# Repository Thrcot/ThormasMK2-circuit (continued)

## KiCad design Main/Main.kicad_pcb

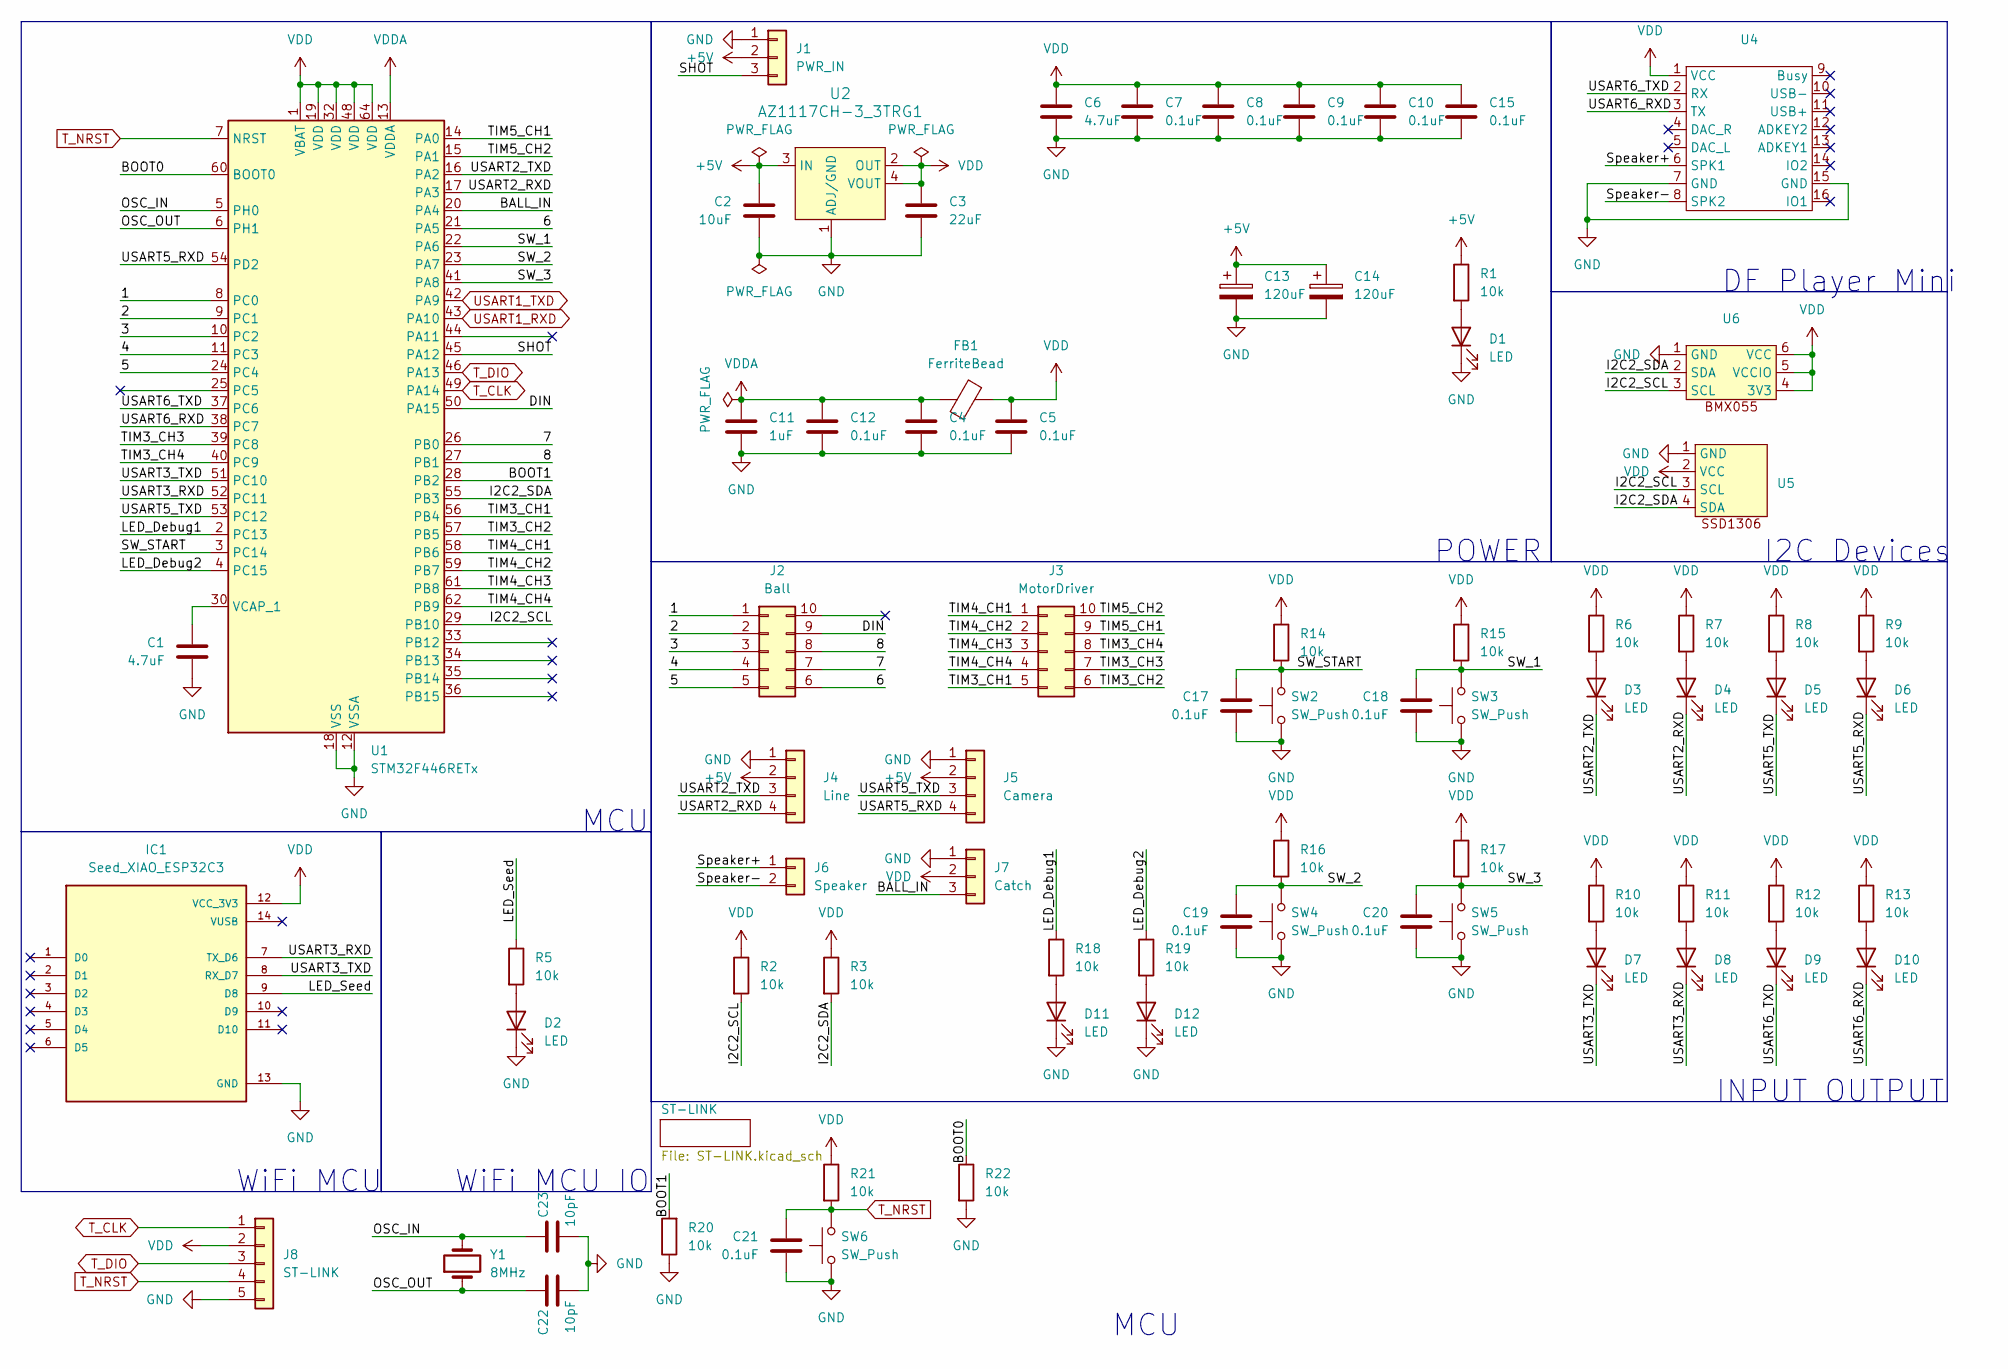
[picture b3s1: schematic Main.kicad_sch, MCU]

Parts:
C1, C6: 4.7uF; C_0603_1608Metric
C2: 10uF; C_0603_1608Metric
C3: 22uF; C_0603_1608Metric
C4, C5, C7, C8, C9, C10, C12, C15, C17, C18, C19, C20, C21: 0.1uF; C_0402_1005Metric
C11: 1uF; C_0603_1608Metric
C13, C14: 120uF; CP_Radial_D10.0mm_P5.00mm
C22, C23: 10pF; C_0402_1005Metric
D1, D2, D3, D4, D5, D6, D7, D8, D9, D10, D11, D12: LED; LED_0603_1608Metric
FB1: FerriteBead; L_0603_1608Metric
IC1: Seed_XIAO_ESP32C3; PARTREV 23/05/2022
J1: PWR_IN; JST_XH_S3B-XH-A_1x03_P2.50mm_Horizontal
J2: Ball; IDC-Header_2x05_P2.54mm_Vertical
J3: MotorDriver; IDC-Header_2x05_P2.54mm_Vertical
J4: Line; JST_XH_S4B-XH-A_1x04_P2.50mm_Horizontal
J5: Camera; JST_XH_S4B-XH-A_1x04_P2.50mm_Horizontal
J6: Speaker; JST_XH_B2B-XH-A_1x02_P2.50mm_Vertical
J7: Catch; JST_XH_S3B-XH-A_1x03_P2.50mm_Horizontal
J8: ST-LINK; PinHeader_1x05_P2.54mm_Horizontal
R1, R2, R3, R5, R6, R7, R8, R9, R10, R11, R12, R13, R14, R15, R16, R17, R18, R19, R20, R21, R22: 10k; R_0603_1608Metric
SW2, SW3, SW4, SW5, SW6: SW_Push; SW_PUSH_6mm
U1: STM32F446RETx; LQFP-64_10x10mm_P0.5mm
U2: AZ1117CH-3_3TRG1; SOT-223; MPN AZ1117CH-3.3TRG1
U4: DFPlayerMini
U5: SSD1306
U6: BMX055DIP
Y1: 8MHz; Crystal_HC49-4H_Vertical

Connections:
+5V: C2.1, C13.1, C14.1, J1.2, J4.2, J5.2, R1.1, U2.3 (IN); also elsewhere on the board
/1: J2.1, U1.8 (PC0)
/2: J2.2, U1.9 (PC1)
/3: J2.3, U1.10 (PC2)
/4: J2.4, U1.11 (PC3)
/5: J2.5, U1.24 (PC4)
/6: J2.6, U1.21 (PA5)
/7: J2.7, U1.26 (PB0)
/8: J2.8, U1.27 (PB1)
/BALL_IN: J7.3, U1.20 (PA4)
/BOOT0: R22.1, U1.60 (BOOT0)
/BOOT1: R20.2, U1.28 (PB2)
/DIN: J2.9, U1.50 (PA15)
/I2C2_SCL: R2.2, U1.29 (PB10), U5.3 (SCL), U6.3 (SCL)
/I2C2_SDA: R3.2, U1.55 (PB3), U5.4 (SDA), U6.2 (SDA)
/LED_Debug1: R18.1, U1.2 (PC13)
/LED_Debug2: R19.1, U1.4 (PC15)
/LED_Seed: IC1.9 (D8), R5.1
/OSC_IN: C23.1, U1.5 (PH0), Y1.2
/OSC_OUT: C22.1, U1.6 (PH1), Y1.1
/SHOT: J1.3, U1.45 (PA12)
/SW_1: C18.1, R15.2, SW3.2, U1.22 (PA6)
/SW_2: C19.1, R16.2, SW4.2, U1.23 (PA7)
/SW_3: C20.1, R17.2, SW5.2, U1.41 (PA8)
/SW_START: C17.1, R14.2, SW2.2, U1.3 (PC14)
/Speaker+: J6.1, U4.6 (SPK1)
/Speaker-: J6.2, U4.8 (SPK2)
/TIM3_CH1: J3.5, U1.56 (PB4)
/TIM3_CH2: J3.6, U1.57 (PB5)
/TIM3_CH3: J3.7, U1.39 (PC8)
/TIM3_CH4: J3.8, U1.40 (PC9)
/TIM4_CH1: J3.1, U1.58 (PB6)
/TIM4_CH2: J3.2, U1.59 (PB7)
/TIM4_CH3: J3.3, U1.61 (PB8)
/TIM4_CH4: J3.4, U1.62 (PB9)
/TIM5_CH1: J3.9, U1.14 (PA0)
/TIM5_CH2: J3.10, U1.15 (PA1)
/USART2_RXD: D4.1 (K), J4.4, U1.17 (PA3)
/USART2_TXD: D3.1 (K), J4.3, U1.16 (PA2)
/USART3_RXD: D8.1 (K), IC1.7 (TX_D6), U1.52 (PC11)
/USART3_TXD: D7.1 (K), IC1.8 (RX_D7), U1.51 (PC10)
/USART5_RXD: D6.1 (K), J5.4, U1.54 (PD2)
/USART5_TXD: D5.1 (K), J5.3, U1.53 (PC12)
/USART6_RXD: D10.1 (K), U1.38 (PC7), U4.3 (TX)
/USART6_TXD: D9.1 (K), U1.37 (PC6), U4.2 (RX)
GND: C1.2, C2.2, C3.2, C4.2, C5.2, C6.2, C7.2, C8.2, C9.2, C10.2, C11.2, C12.2, C13.2, C14.2, C15.2, C17.2, C18.2, C19.2, C20.2, C21.2, C22.2, C23.2, D1.1 (K), D2.1 (K), D11.1 (K), D12.1 (K), IC1.13 (GND), J1.1, J4.1, J5.1, J7.1, J8.5, R20.1, R22.2, SW2.1, SW3.1, SW4.1, SW5.1, SW6.1, U1.12 (VSSA), U1.18 (VSS), U1.31 (VSS), U1.47 (VSS), U1.63 (VSS), U2.1 (ADJ/GND), U4.7 (GND), U4.15 (GND), U5.1 (GND), U6.1 (GND); also elsewhere on the board
unnamed: D1.2 (A), R1.2
unnamed: D2.2 (A), R5.2
unnamed: D3.2 (A), R6.2
unnamed: D4.2 (A), R7.2
unnamed: D5.2 (A), R8.2
unnamed: D6.2 (A), R9.2
unnamed: D7.2 (A), R10.2
unnamed: D8.2 (A), R11.2
unnamed: D9.2 (A), R12.2
unnamed: D10.2 (A), R13.2
unnamed: D11.2 (A), R18.2
unnamed: D12.2 (A), R19.2
unnamed: C1.1, U1.30 (VCAP_1)
T_CLK: J8.1, U1.49 (PA14); also elsewhere on the board
T_DIO: J8.3, U1.46 (PA13); also elsewhere on the board
T_NRST: C21.1, J8.4, R21.2, SW6.2, U1.7 (NRST); also elsewhere on the board
USART1_RXD: U1.43 (PA10); also elsewhere on the board
USART1_TXD: U1.42 (PA9); also elsewhere on the board
VDD: C3.1, C5.1, C6.1, C7.1, C8.1, C9.1, C10.1, C15.1, FB1.2, IC1.12 (VCC_3V3), J7.2, J8.2, R2.1, R3.1, R6.1, R7.1, R8.1, R9.1, R10.1, R11.1, R12.1, R13.1, R14.1, R15.1, R16.1, R17.1, R21.1, U1.1 (VBAT), U1.19 (VDD), U1.32 (VDD), U1.48 (VDD), U1.64 (VDD), U2.2 (OUT), U2.4 (VOUT), U4.1 (VCC), U5.2 (VCC), U6.4 (3V3), U6.5 (VCCIO), U6.6 (VCC); also elsewhere on the board
VDDA: C4.1, C11.1, C12.1, FB1.1, U1.13 (VDDA)

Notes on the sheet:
WiFi MCU IO
MCU
POWER
INPUT OUTPUT
DF Player Mini
WiFi MCU
I2C Devices

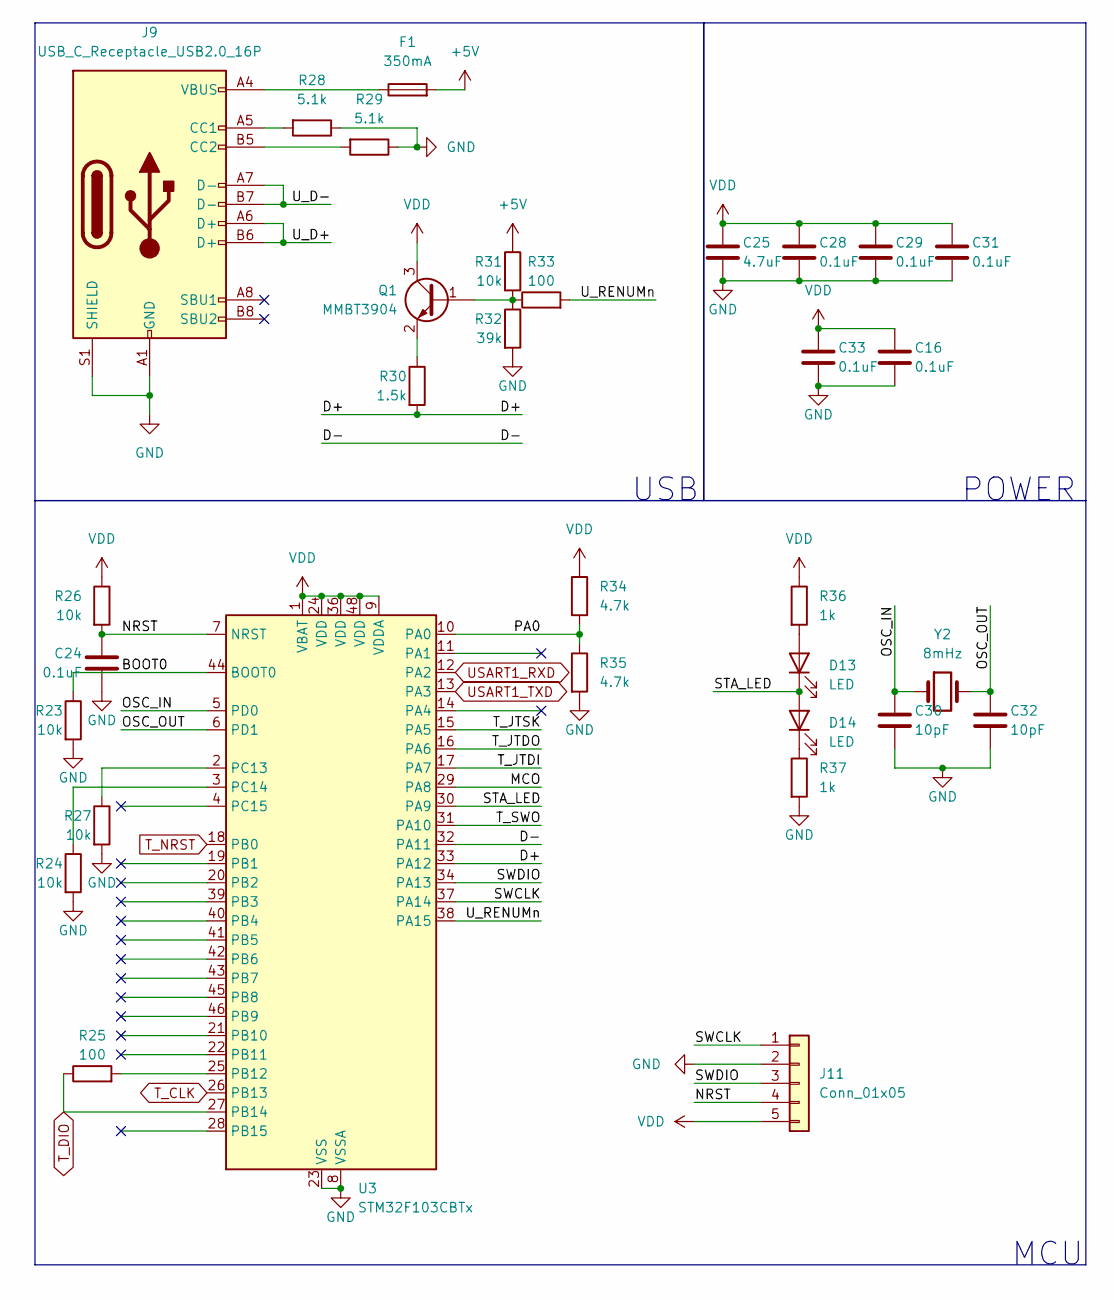
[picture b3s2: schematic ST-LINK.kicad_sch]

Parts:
C16, C24, C28, C29, C31, C33: 0.1uF; C_0402_1005Metric
C25: 4.7uF; C_0603_1608Metric
C30, C32: 10pF; C_0402_1005Metric
D13, D14: LED; LED_0603_1608Metric
F1: 350mA; Fuse_0402_1005Metric
J9: USB_C_Receptacle_USB2.0_16P; USB_C_Receptacle_GCT_USB4105-xx-A_16P_TopMnt_Horizontal
J11: Conn_01x05; PinHeader_1x05_P2.54mm_Vertical
Q1: MMBT3904; SOT-23
R23, R24, R26, R27, R31: 10k; R_0603_1608Metric
R25, R33: 100; R_0603_1608Metric
R28, R29: 5.1k; R_0603_1608Metric
R30: 1.5k; R_0603_1608Metric
R32: 39k; R_0603_1608Metric
R34, R35: 4.7k; R_0603_1608Metric
R36, R37: 1k; R_0603_1608Metric
U3: STM32F103CBTx; LQFP-48_7x7mm_P0.5mm
Y2: 8mHz; Crystal_HC49-4H_Vertical

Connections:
+5V: F1.2, R31.1; also elsewhere on the board
/ST-LINK/BOOT0: R23.1, U3.44 (BOOT0)
/ST-LINK/D+: R30.2, U3.33 (PA12)
/ST-LINK/D-: U3.32 (PA11)
/ST-LINK/MCO: U3.29 (PA8)
/ST-LINK/NRST: C24.1, J11.4, R26.2, U3.7 (NRST)
/ST-LINK/OSC_IN: C30.1, U3.5 (PD0), Y2.1
/ST-LINK/OSC_OUT: C32.1, U3.6 (PD1), Y2.2
/ST-LINK/PA0: R34.2, R35.1, U3.10 (PA0)
/ST-LINK/STA_LED: D13.1 (K), D14.2 (A), U3.30 (PA9)
/ST-LINK/SWCLK: J11.1, U3.37 (PA14)
/ST-LINK/SWDIO: J11.3, U3.34 (PA13)
/ST-LINK/T_JTDI: U3.17 (PA7)
/ST-LINK/T_JTDO: U3.16 (PA6)
/ST-LINK/T_JTSK: U3.15 (PA5)
/ST-LINK/T_SWO: U3.31 (PA10)
/ST-LINK/U_D+: J9.A6 (D+), J9.B6 (D+)
/ST-LINK/U_D-: J9.A7 (D-), J9.B7 (D-)
/ST-LINK/U_RENUMn: R33.2, U3.38 (PA15)
GND: C16.2, C24.2, C25.2, C28.2, C29.2, C30.2, C31.2, C32.2, C33.2, J9.A1 (GND), J9.A12 (GND), J9.B1 (GND), J9.B12 (GND), J9.S1 (SHIELD), J11.2, R23.2, R24.2, R27.2, R28.1, R29.1, R32.2, R35.2, R37.2, U3.8 (VSSA), U3.23 (VSS), U3.35 (VSS), U3.47 (VSS); also elsewhere on the board
unnamed: D13.2 (A), R36.2
unnamed: D14.1 (K), R37.1
unnamed: F1.1, J9.A4 (VBUS), J9.A9 (VBUS), J9.B4 (VBUS), J9.B9 (VBUS)
unnamed: J9.A5 (CC1), R28.2
unnamed: J9.B5 (CC2), R29.2
unnamed: Q1.1 (B), R31.2, R32.1, R33.1
unnamed: Q1.2 (E), R30.1
unnamed: R25.2, U3.25 (PB12)
unnamed: R27.1, U3.2 (PC13)
unnamed: R24.1, U3.3 (PC14)
T_CLK: U3.26 (PB13); also elsewhere on the board
T_DIO: R25.1, U3.27 (PB14); also elsewhere on the board
T_NRST: U3.18 (PB0); also elsewhere on the board
USART1_RXD: U3.12 (PA2); also elsewhere on the board
USART1_TXD: U3.13 (PA3); also elsewhere on the board
VDD: C16.1, C25.1, C28.1, C29.1, C31.1, C33.1, J11.5, Q1.3 (C), R26.1, R34.1, R36.1, U3.1 (VBAT), U3.9 (VDDA), U3.24 (VDD), U3.36 (VDD), U3.48 (VDD); also elsewhere on the board

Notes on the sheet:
MCU
POWER
USB

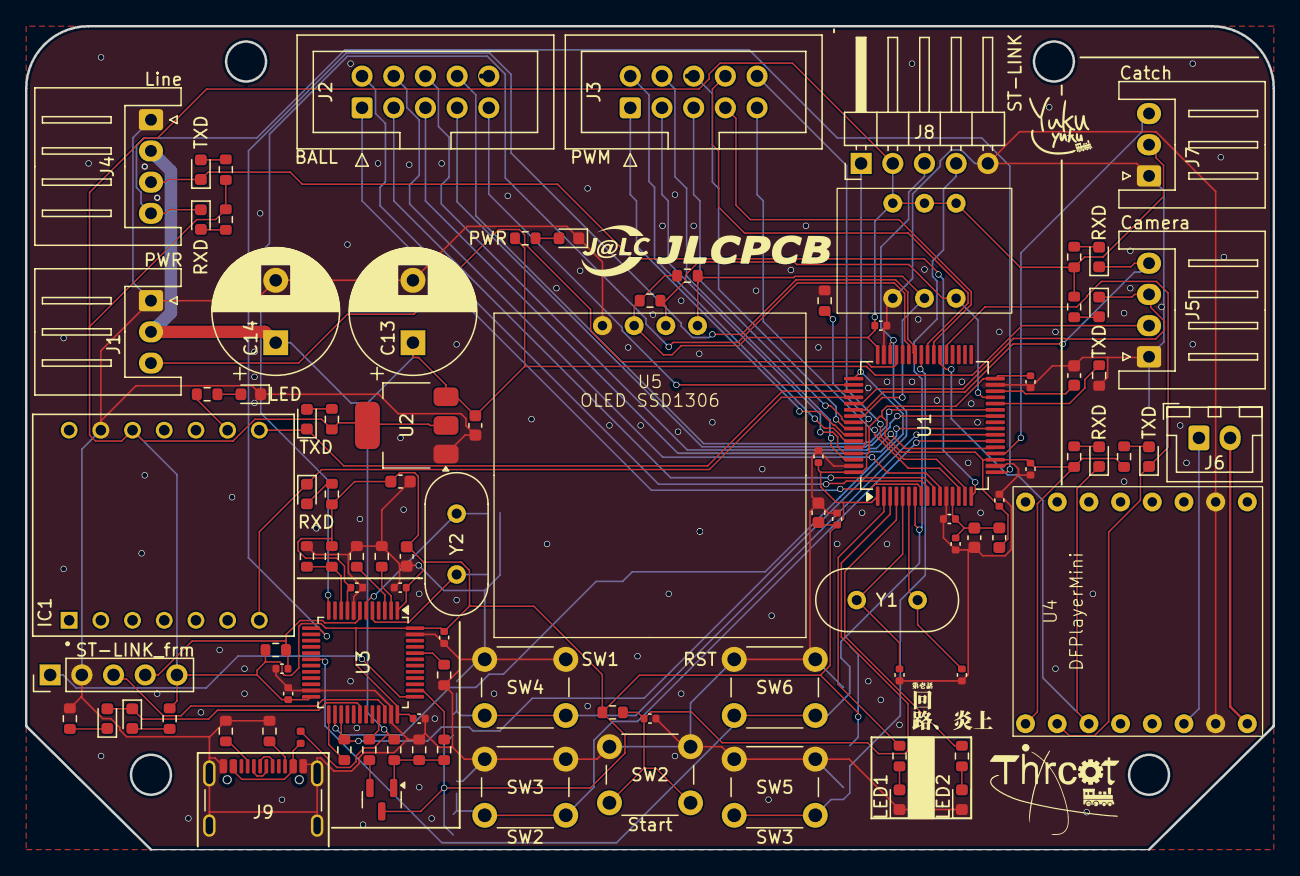
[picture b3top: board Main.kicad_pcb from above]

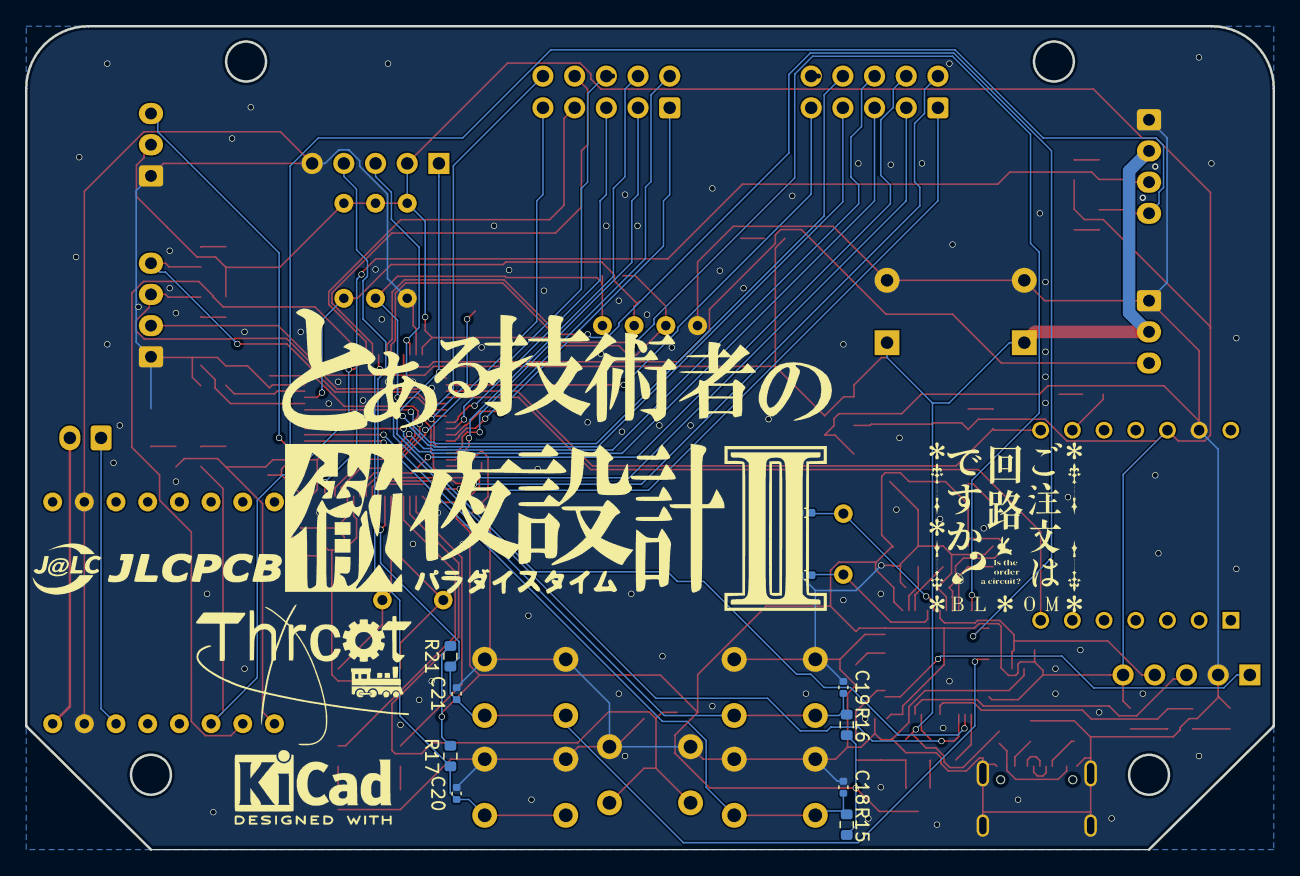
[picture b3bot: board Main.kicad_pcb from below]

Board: 2 copper layers, 100.0 x 66.0 mm, 108 parts (10 on the bottom side), 88 nets.

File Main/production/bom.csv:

Designator,Footprint,Quantity,Value,LCSC Part #
"C1, C25, C6",0603,3,4.7uF,
"C10, C12, C15, C16, C17, C18, C19, C20, C21, C24, C28, C29, C31, C33, C4, C5, C7, C8, C9",0402,19,0.1uF,
C11,0603,1,1uF,
"C13, C14",CP_Radial_D10.0mm_P5.00mm,2,120uF,
C2,0603,1,10uF,
"C22, C23, C30, C32",0402,4,10pF,
C3,0603,1,22uF,
"D1, D10, D11, D12, D13, D14, D2, D3, D4, D5, D6, D7, D8, D9",0603,14,LED,
F1,0402,1,350mA,
FB1,0603,1,FerriteBead,
IC1,Seed_XIAO_ESP32C3,1,Seed_XIAO_ESP32C3,
J1,JST_XH_S3B-XH-A_1x03_P2.50mm_Horizontal,1,PWR_IN,
J11,PinHeader_1x05_P2.54mm_Vertical,1,Conn_01x05,
J2,IDC-Header_2x05_P2.54mm_Vertical,1,Ball,
J3,IDC-Header_2x05_P2.54mm_Vertical,1,MotorDriver,
J4,JST_XH_S4B-XH-A_1x04_P2.50mm_Horizontal,1,Line,
J5,JST_XH_S4B-XH-A_1x04_P2.50mm_Horizontal,1,Camera,
J6,JST_XH_B2B-XH-A_1x02_P2.50mm_Vertical,1,Speaker,
J7,JST_XH_S3B-XH-A_1x03_P2.50mm_Horizontal,1,Catch,
J8,PinHeader_1x05_P2.54mm_Horizontal,1,ST-LINK,
J9,USB_C_Receptacle_GCT_USB4105-xx-A_16P_TopMnt_Horizontal,1,USB_C_Receptacle_USB2.0_16P,
Q1,SOT-23,1,MMBT3904,
"R1, R10, R11, R12, R13, R14, R15, R16, R17, R18, R19, R2, R20, R21, R22, R23, R24, R26, R27, R3, R31, R5, R6, R7, R8, R9",0603,26,10k,
"R25, R33",0603,2,100,
"R28, R29",0603,2,5.1k,
R30,0603,1,1.5k,
R32,0603,1,39k,
"R34, R35",0603,2,4.7k,
"R36, R37",0603,2,1k,
"SW2, SW3, SW4, SW5, SW6",SW_PUSH_6mm,5,SW_Push,
U1,LQFP-64_10x10mm_P0.5mm,1,STM32F446RETx,
U2,SOT-223,1,AZ1117CH-3_3TRG1,AZ1117CH-3.3TRG1
U3,LQFP-48_7x7mm_P0.5mm,1,STM32F103CBTx,
U4,DFPlayerMini,1,~,
U5,SSD1306,1,~,
U6,BMX055DIP,1,~,
"Y1, Y2",Crystal_HC49-4H_Vertical,2,8MHz,

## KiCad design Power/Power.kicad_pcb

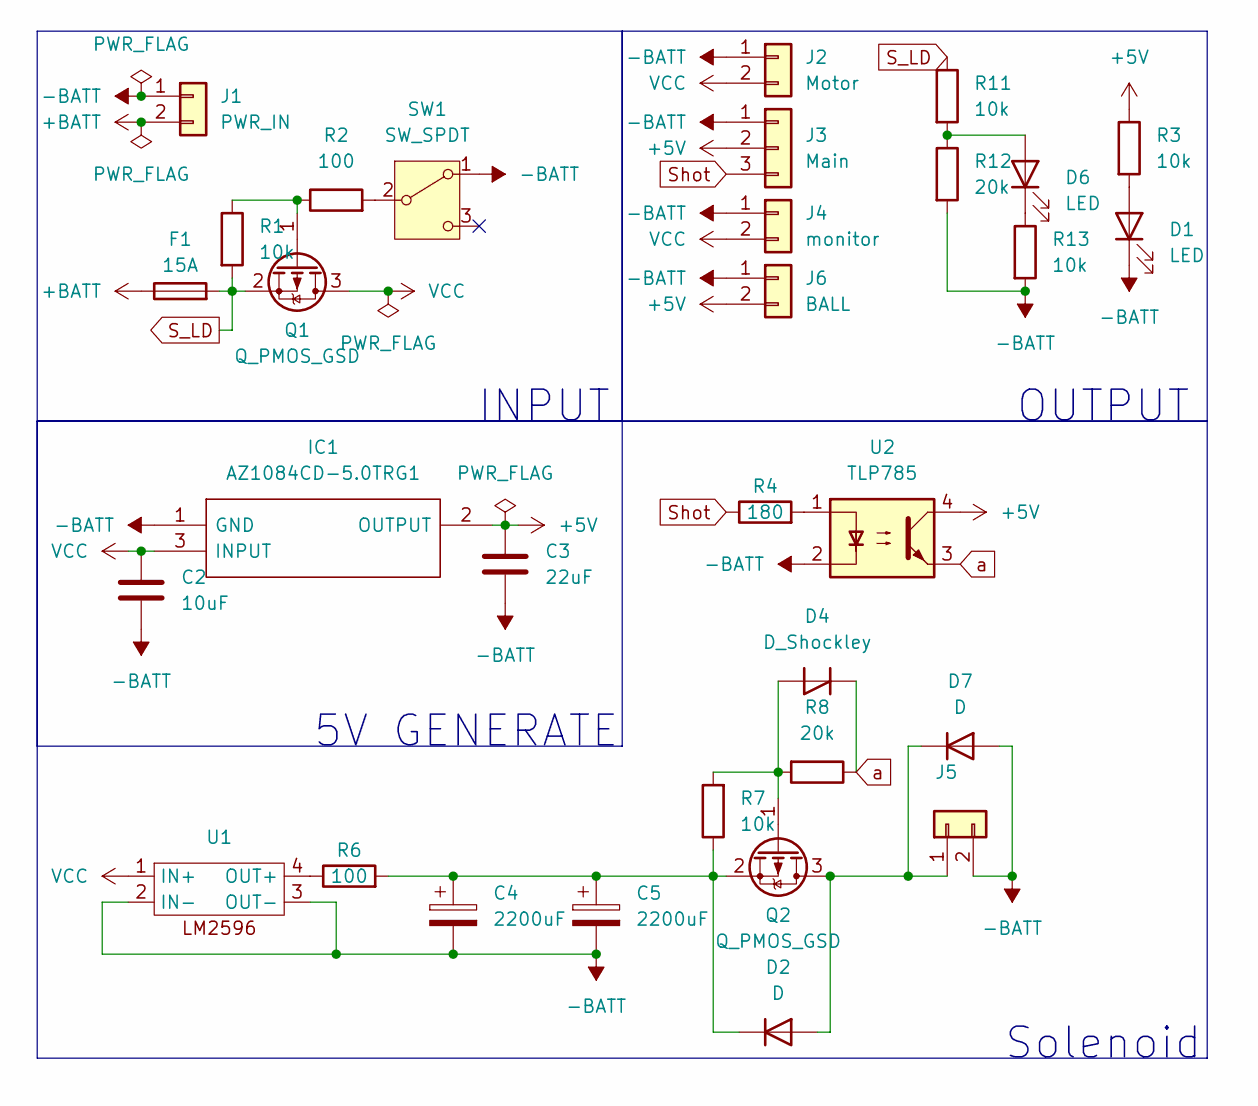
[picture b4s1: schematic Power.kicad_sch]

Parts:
C2: 10uF; C_0603_1608Metric
C3: 22uF; C_0603_1608Metric
C4, C5: 2200uF; CP_Radial_D22.0mm_P10.00mm_SnapIn
D1, D6: LED; LED_0603_1608Metric
D2, D7: D; D_SOD-123
D4: D_Shockley; D_SMC
F1: 15A; Fuseholder_Clip-6.3x32mm_Littelfuse_102_122_Inline_P34.21x7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
IC1: AZ1084CD-5.0TRG1; AZ1084CD50TRG1; Mouser Part Number 621-AZ1084CD-5.0TRG1
J1: PWR_IN; AMASS_XT30U-M_1x02_P5.0mm_Vertical
J2: Motor; AMASS_XT30U-F_1x02_P5.0mm_Vertical
J3: Main; JST_XH_B3B-XH-A_1x03_P2.50mm_Vertical
J4: monitor; PinHeader_1x02_P2.00mm_Vertical
J5: Conn_01x02; AMASS_XT30U-M_1x02_P5.0mm_Vertical
J6: BALL; JST_XH_B2B-XH-A_1x02_P2.50mm_Vertical
Q1, Q2: Q_PMOS_GSD; TO-252-2
R1, R3, R7, R11, R13: 10k; R_0603_1608Metric
R2, R6: 100; R_0603_1608Metric
R4: 180; R_0603_1608Metric
R8, R12: 20k; R_0603_1608Metric
SW1: SW_SPDT; PinHeader_1x03_P2.54mm_Vertical
U1: LM2596
U2: TLP785; DIP-4_W7.62mm

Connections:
+5V: C3.1, IC1.2 (OUTPUT), J3.2, J6.2, R3.1, U2.4
+BATT: F1.1, J1.2
-BATT: C2.2, C3.2, C4.2, C5.2, D1.1 (K), D7.2 (A), IC1.1 (GND), J1.1, J2.1, J3.1, J4.1, J5.2, J6.1, R12.2, R13.2, SW1.1 (A), U1.2 (IN-), U1.3 (OUT-), U2.2
unnamed: D1.2 (A), R3.2
unnamed: D2.2 (A), D7.1 (K), J5.1, Q2.3 (D)
unnamed: C4.1, C5.1, D2.1 (K), Q2.2 (S), R6.2, R7.1
unnamed: D4.2 (A), Q2.1 (G), R7.2, R8.2
unnamed: D6.2 (A), R11.2, R12.1
unnamed: D6.1 (K), R13.1
unnamed: Q1.1 (G), R1.1, R2.1
unnamed: R4.2, U2.1
unnamed: R2.2, SW1.2 (B)
unnamed: R6.1, U1.4 (OUT+)
S_LD: F1.2, Q1.2 (S), R1.2, R11.1
Shot: J3.3, R4.1
VCC: C2.1, IC1.3 (INPUT), J2.2, J4.2, Q1.3 (D), U1.1 (IN+)
a: D4.1 (K), R8.1, U2.3

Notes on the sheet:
INPUT
OUTPUT
Solenoid
5V GENERATE

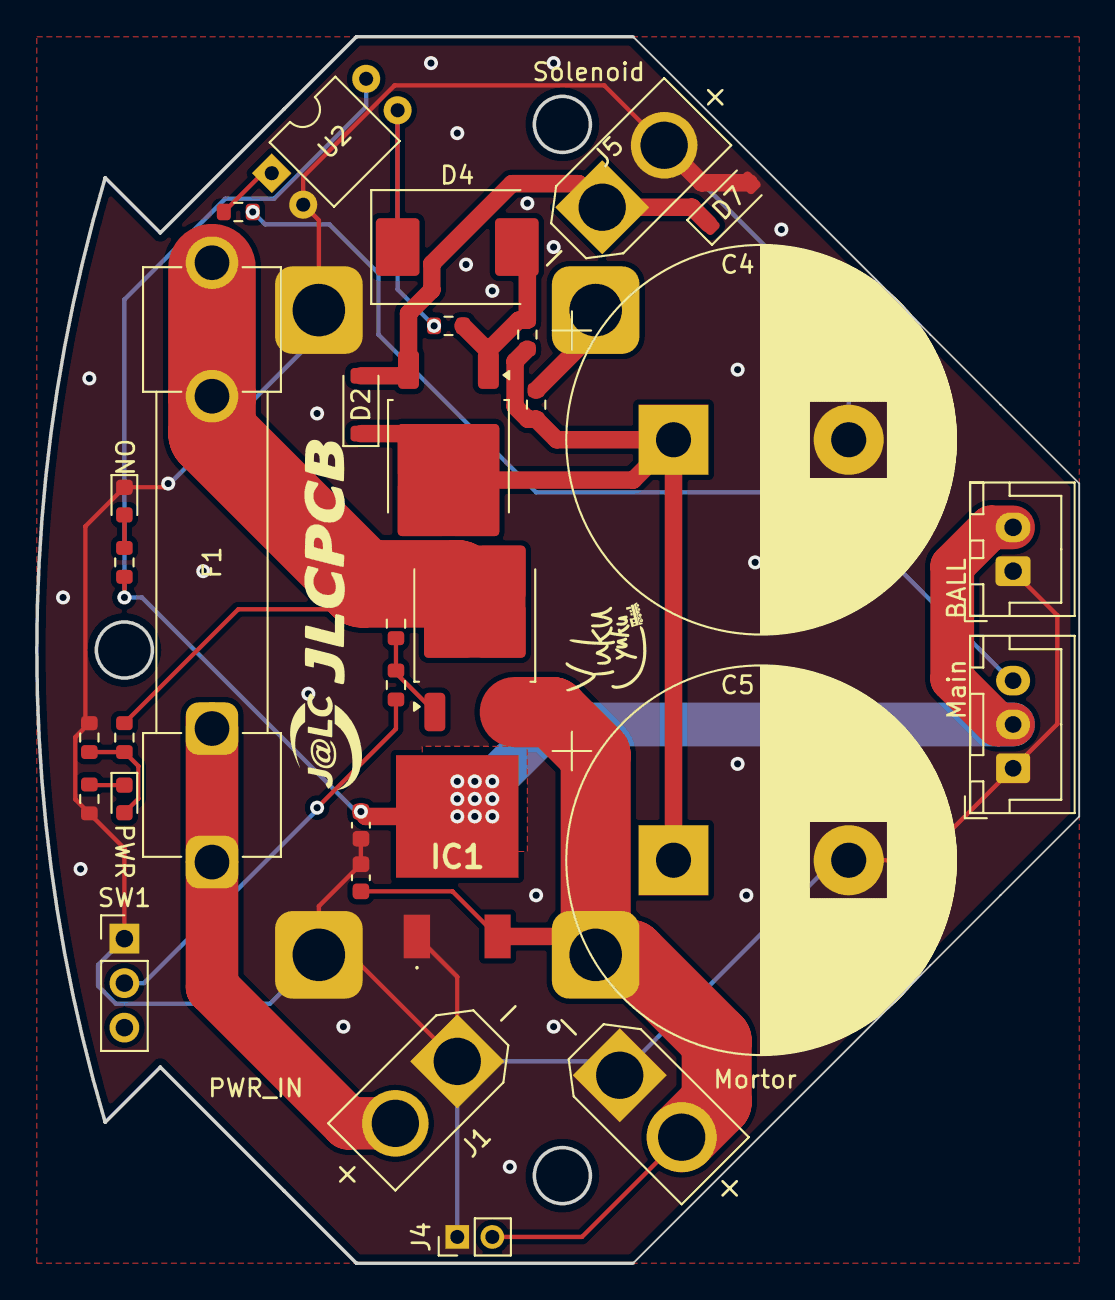
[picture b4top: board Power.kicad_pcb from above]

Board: 2 copper layers, 59.5 x 70.0 mm, 32 parts (1 on the bottom side), 17 nets.

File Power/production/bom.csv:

Designator,Footprint,Quantity,Value,LCSC Part #
C2,0603,1,10uF,
C3,0603,1,22uF,
"C4, C5",CP_Radial_D22.0mm_P10.00mm_SnapIn,2,2200uF,
"D1, D6",0603,2,LED,
"D2, D7",D_SOD-123,2,D,
D4,D_SMC,1,D_Shockley,
F1,Fuseholder_Clip-6.3x32mm_Littelfuse_102_122_Inline_P34.21x7.62mm_D1.98mm_Horizontal,1,15A,
IC1,AZ1084CD50TRG1,1,AZ1084CD-5.0TRG1,
J1,AMASS_XT30U-M_1x02_P5.0mm_Vertical,1,PWR_IN,
J2,AMASS_XT30U-F_1x02_P5.0mm_Vertical,1,Motor,
J3,JST_XH_B3B-XH-A_1x03_P2.50mm_Vertical,1,Main,
J4,PinHeader_1x02_P2.00mm_Vertical,1,monitor,
J5,AMASS_XT30U-M_1x02_P5.0mm_Vertical,1,Conn_01x02,
J6,JST_XH_B2B-XH-A_1x02_P2.50mm_Vertical,1,BALL,
"Q1, Q2",TO-252-2,2,Q_PMOS_GSD,
"R1, R11, R13, R3, R7",0603,5,10k,
"R12, R8",0603,2,20k,
"R2, R6",0603,2,100,
R4,0603,1,180,
SW1,PinHeader_1x03_P2.54mm_Vertical,1,SW_SPDT,
U1,LM2596,1,~,
U2,DIP-4_W7.62mm,1,TLP785,

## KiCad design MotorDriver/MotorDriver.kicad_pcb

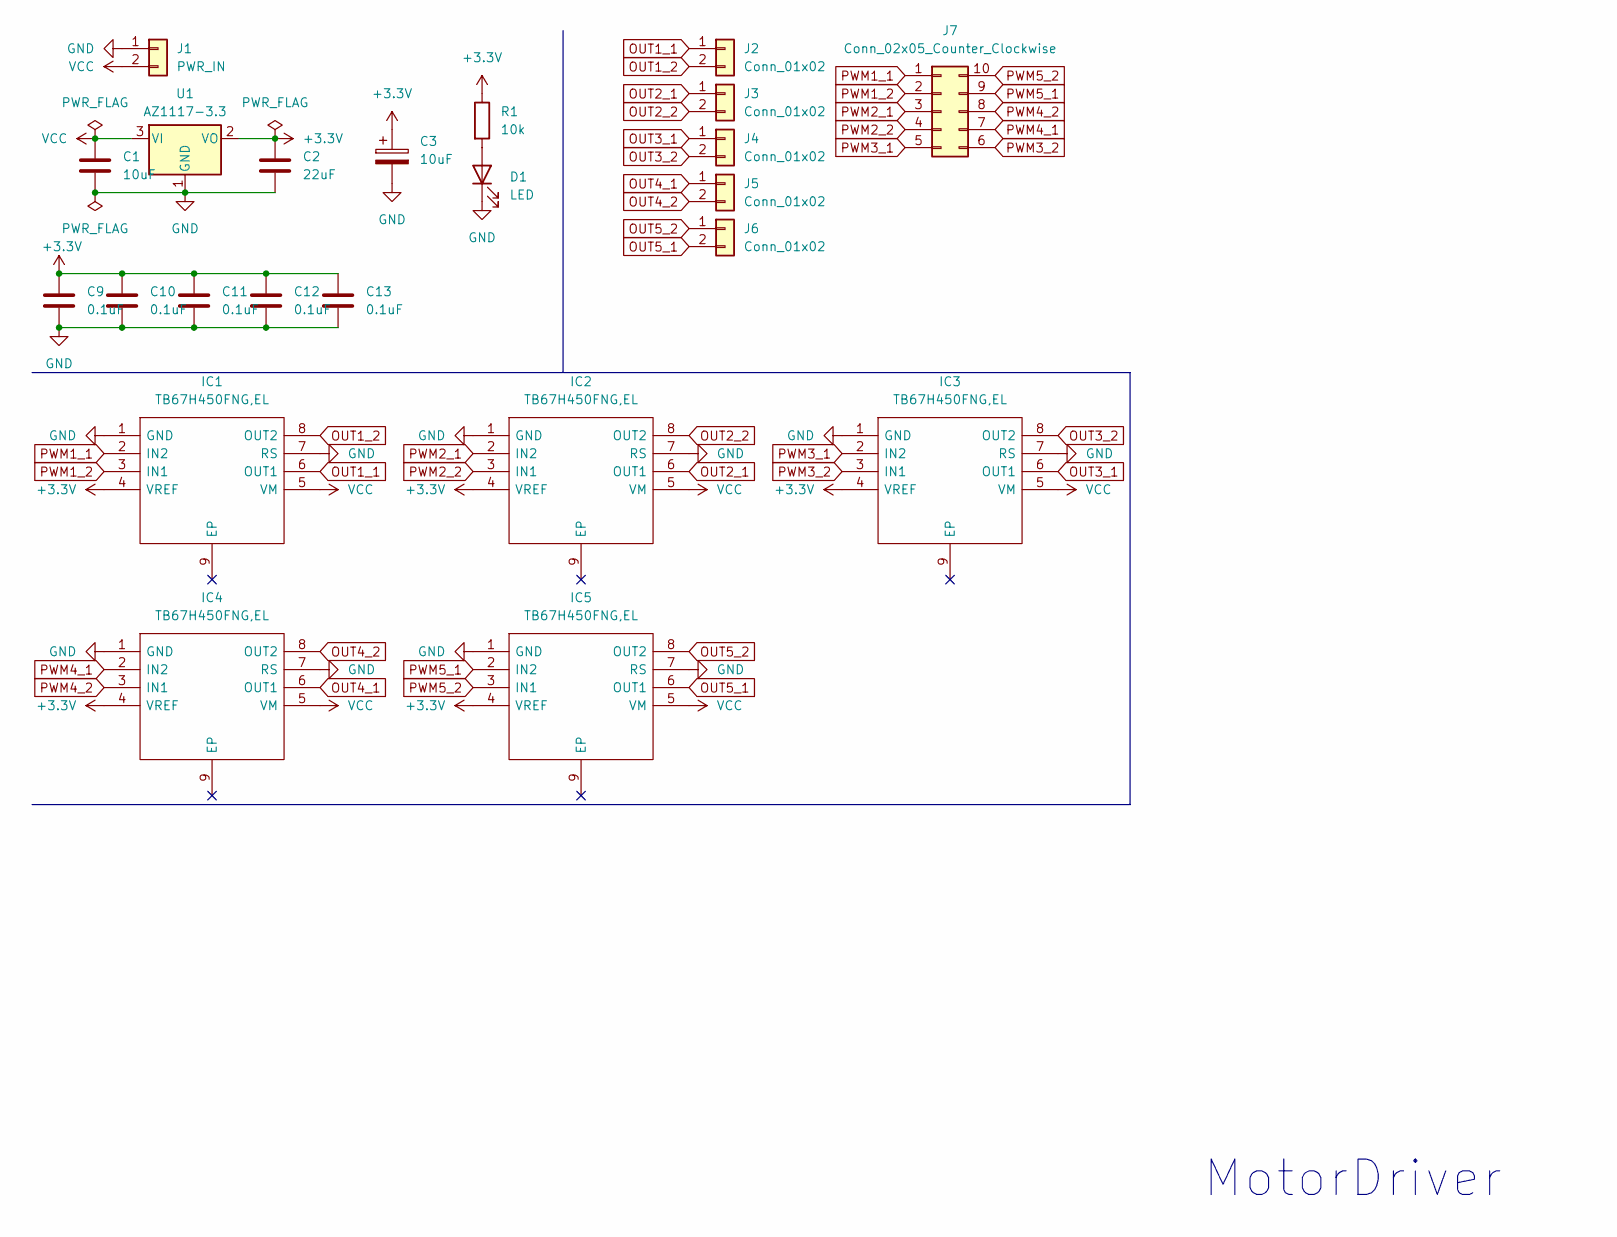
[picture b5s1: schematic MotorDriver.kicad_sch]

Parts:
C1: 10uF; C_0603_1608Metric
C2: 22uF; C_0603_1608Metric
C3: 10uF; CP_Radial_D8.0mm_P5.00mm
C9, C10, C11, C12, C13: 0.1uF; C_0402_1005Metric
D1: LED; LED_0603_1608Metric
IC1, IC2, IC3, IC4, IC5: TB67H450FNG,EL; SOIC127P600X175-9N; Mouser Part Number 757-TB67H450FNGEL
J1: PWR_IN; AMASS_XT30U-M_1x02_P5.0mm_Vertical
J2, J3, J4, J5: Conn_01x02; JST_XH_S2B-XH-A_1x02_P2.50mm_Horizontal
J6: Conn_01x02; JST_XH_B2B-XH-A_1x02_P2.50mm_Vertical
J7: Conn_02x05_Counter_Clockwise; IDC-Header_2x05_P2.54mm_Vertical
R1: 10k; R_0603_1608Metric
U1: AZ1117-3.3; SOT-223-3_TabPin2

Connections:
+3.3V: C2.1, C3.1, C9.1, C10.1, C11.1, C12.1, C13.1, IC1.4 (VREF), IC2.4 (VREF), IC3.4 (VREF), IC4.4 (VREF), IC5.4 (VREF), R1.1, U1.2 (VO)
GND: C1.2, C2.2, C3.2, C9.2, C10.2, C11.2, C12.2, C13.2, D1.1 (K), IC1.1 (GND), IC1.7 (RS), IC2.1 (GND), IC2.7 (RS), IC3.1 (GND), IC3.7 (RS), IC4.1 (GND), IC4.7 (RS), IC5.1 (GND), IC5.7 (RS), J1.1, U1.1 (GND)
unnamed: D1.2 (A), R1.2
OUT1_1: IC1.6 (OUT1), J2.1
OUT1_2: IC1.8 (OUT2), J2.2
OUT2_1: IC2.6 (OUT1), J3.1
OUT2_2: IC2.8 (OUT2), J3.2
OUT3_1: IC3.6 (OUT1), J4.1
OUT3_2: IC3.8 (OUT2), J4.2
OUT4_1: IC4.6 (OUT1), J5.1
OUT4_2: IC4.8 (OUT2), J5.2
OUT5_1: IC5.6 (OUT1), J6.2
OUT5_2: IC5.8 (OUT2), J6.1
PWM1_1: IC1.2 (IN2), J7.1
PWM1_2: IC1.3 (IN1), J7.2
PWM2_1: IC2.2 (IN2), J7.3
PWM2_2: IC2.3 (IN1), J7.4
PWM3_1: IC3.2 (IN2), J7.5
PWM3_2: IC3.3 (IN1), J7.6
PWM4_1: IC4.2 (IN2), J7.7
PWM4_2: IC4.3 (IN1), J7.8
PWM5_1: IC5.2 (IN2), J7.9
PWM5_2: IC5.3 (IN1), J7.10
VCC: C1.1, IC1.5 (VM), IC2.5 (VM), IC3.5 (VM), IC4.5 (VM), IC5.5 (VM), J1.2, U1.3 (VI)

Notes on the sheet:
MotorDriver

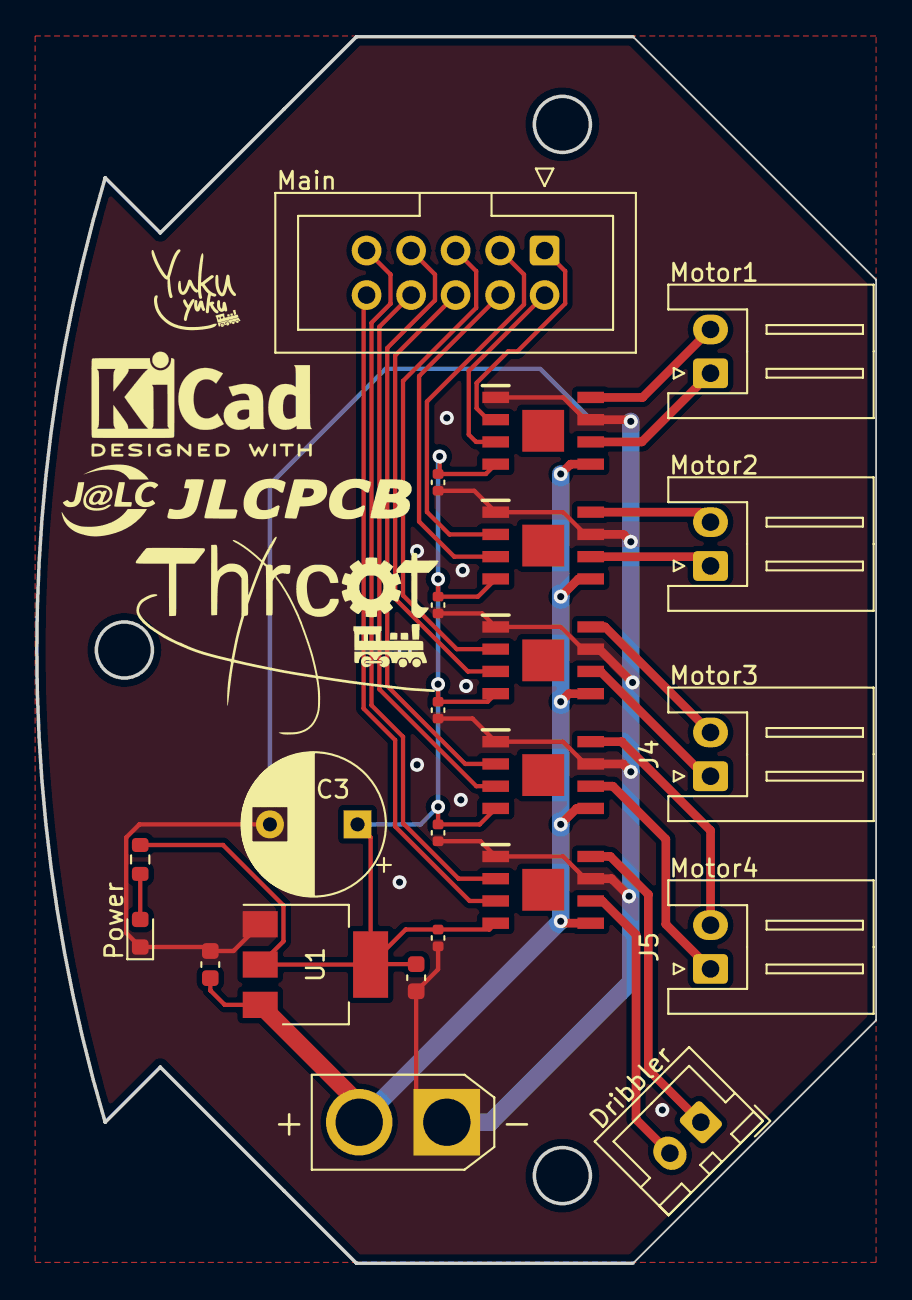
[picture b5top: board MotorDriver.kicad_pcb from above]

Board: 2 copper layers, 47.9 x 70.0 mm, 23 parts (0 on the bottom side), 24 nets.

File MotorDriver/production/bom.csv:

Designator,Footprint,Quantity,Value,LCSC Part #
C1,0603,1,10uF,
"C10, C11, C12, C13, C9",0402,5,0.1uF,
C2,0603,1,22uF,
C3,CP_Radial_D8.0mm_P5.00mm,1,10uF,
D1,0603,1,LED,
"IC1, IC2, IC3, IC4, IC5",SOIC127P600X175-9N,5,"TB67H450FNG,EL",
J1,AMASS_XT30U-M_1x02_P5.0mm_Vertical,1,PWR_IN,
"J2, J3, J4, J5",JST_XH_S2B-XH-A_1x02_P2.50mm_Horizontal,4,Conn_01x02,
J6,JST_XH_B2B-XH-A_1x02_P2.50mm_Vertical,1,Conn_01x02,
J7,IDC-Header_2x05_P2.54mm_Vertical,1,Conn_02x05_Counter_Clockwise,
R1,0603,1,10k,
U1,SOT-223-3_TabPin2,1,AZ1117-3.3,

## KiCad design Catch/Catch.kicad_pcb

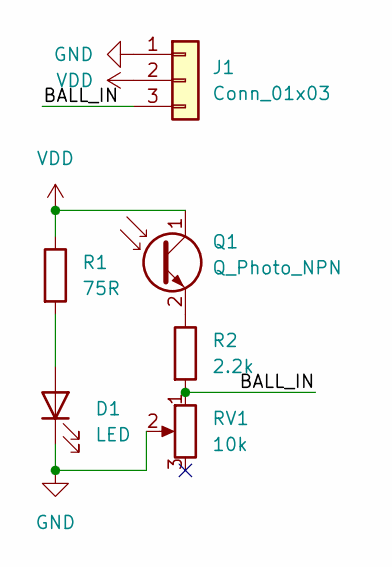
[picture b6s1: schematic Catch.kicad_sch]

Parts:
D1: LED; LED_D5.0mm
J1: Conn_01x03; JST_XH_B3B-XH-A_1x03_P2.50mm_Vertical
Q1: Q_Photo_NPN; LED_D3.0mm_Clear
R1: 75R; R_Axial_DIN0204_L3.6mm_D1.6mm_P5.08mm_Horizontal
R2: 2.2k; R_0603_1608Metric
RV1: 10k; Potentiometer_Bourns_TC33X_Vertical

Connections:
/BALL_IN: J1.3, R2.2, RV1.1
GND: D1.1 (K), J1.1, RV1.2
unnamed: D1.2 (A), R1.2
unnamed: Q1.2 (E), R2.1
VDD: J1.2, Q1.1 (C), R1.1

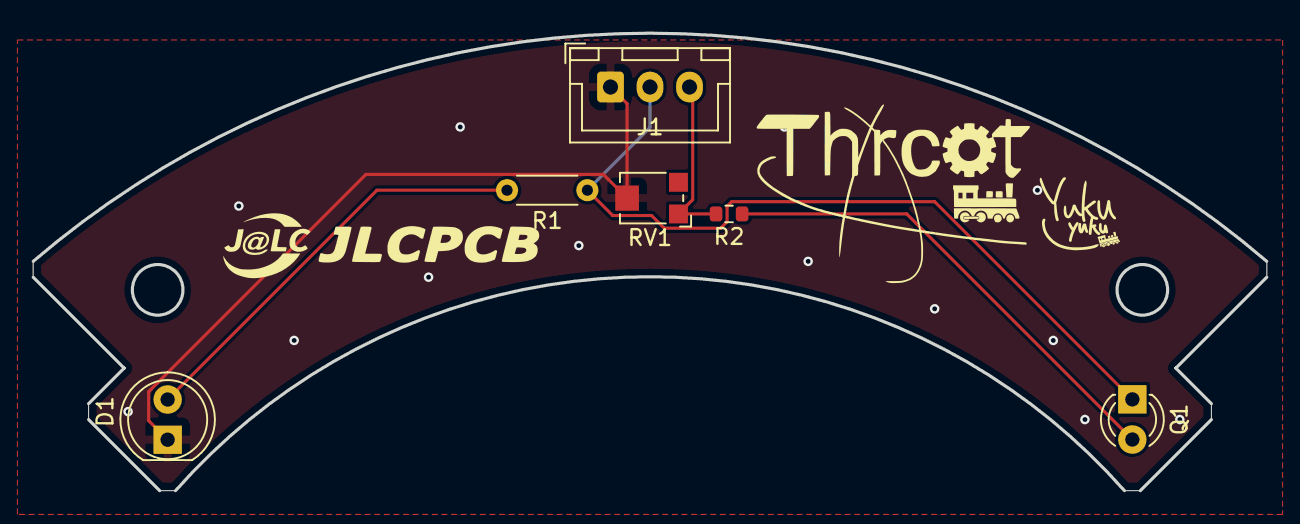
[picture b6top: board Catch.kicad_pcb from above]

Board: 2 copper layers, 78.0 x 28.9 mm, 6 parts (0 on the bottom side), 5 nets.

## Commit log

2024-07-21 Ver-1.0
2024-07-24 Ver-1.2
2024-07-31 finally
